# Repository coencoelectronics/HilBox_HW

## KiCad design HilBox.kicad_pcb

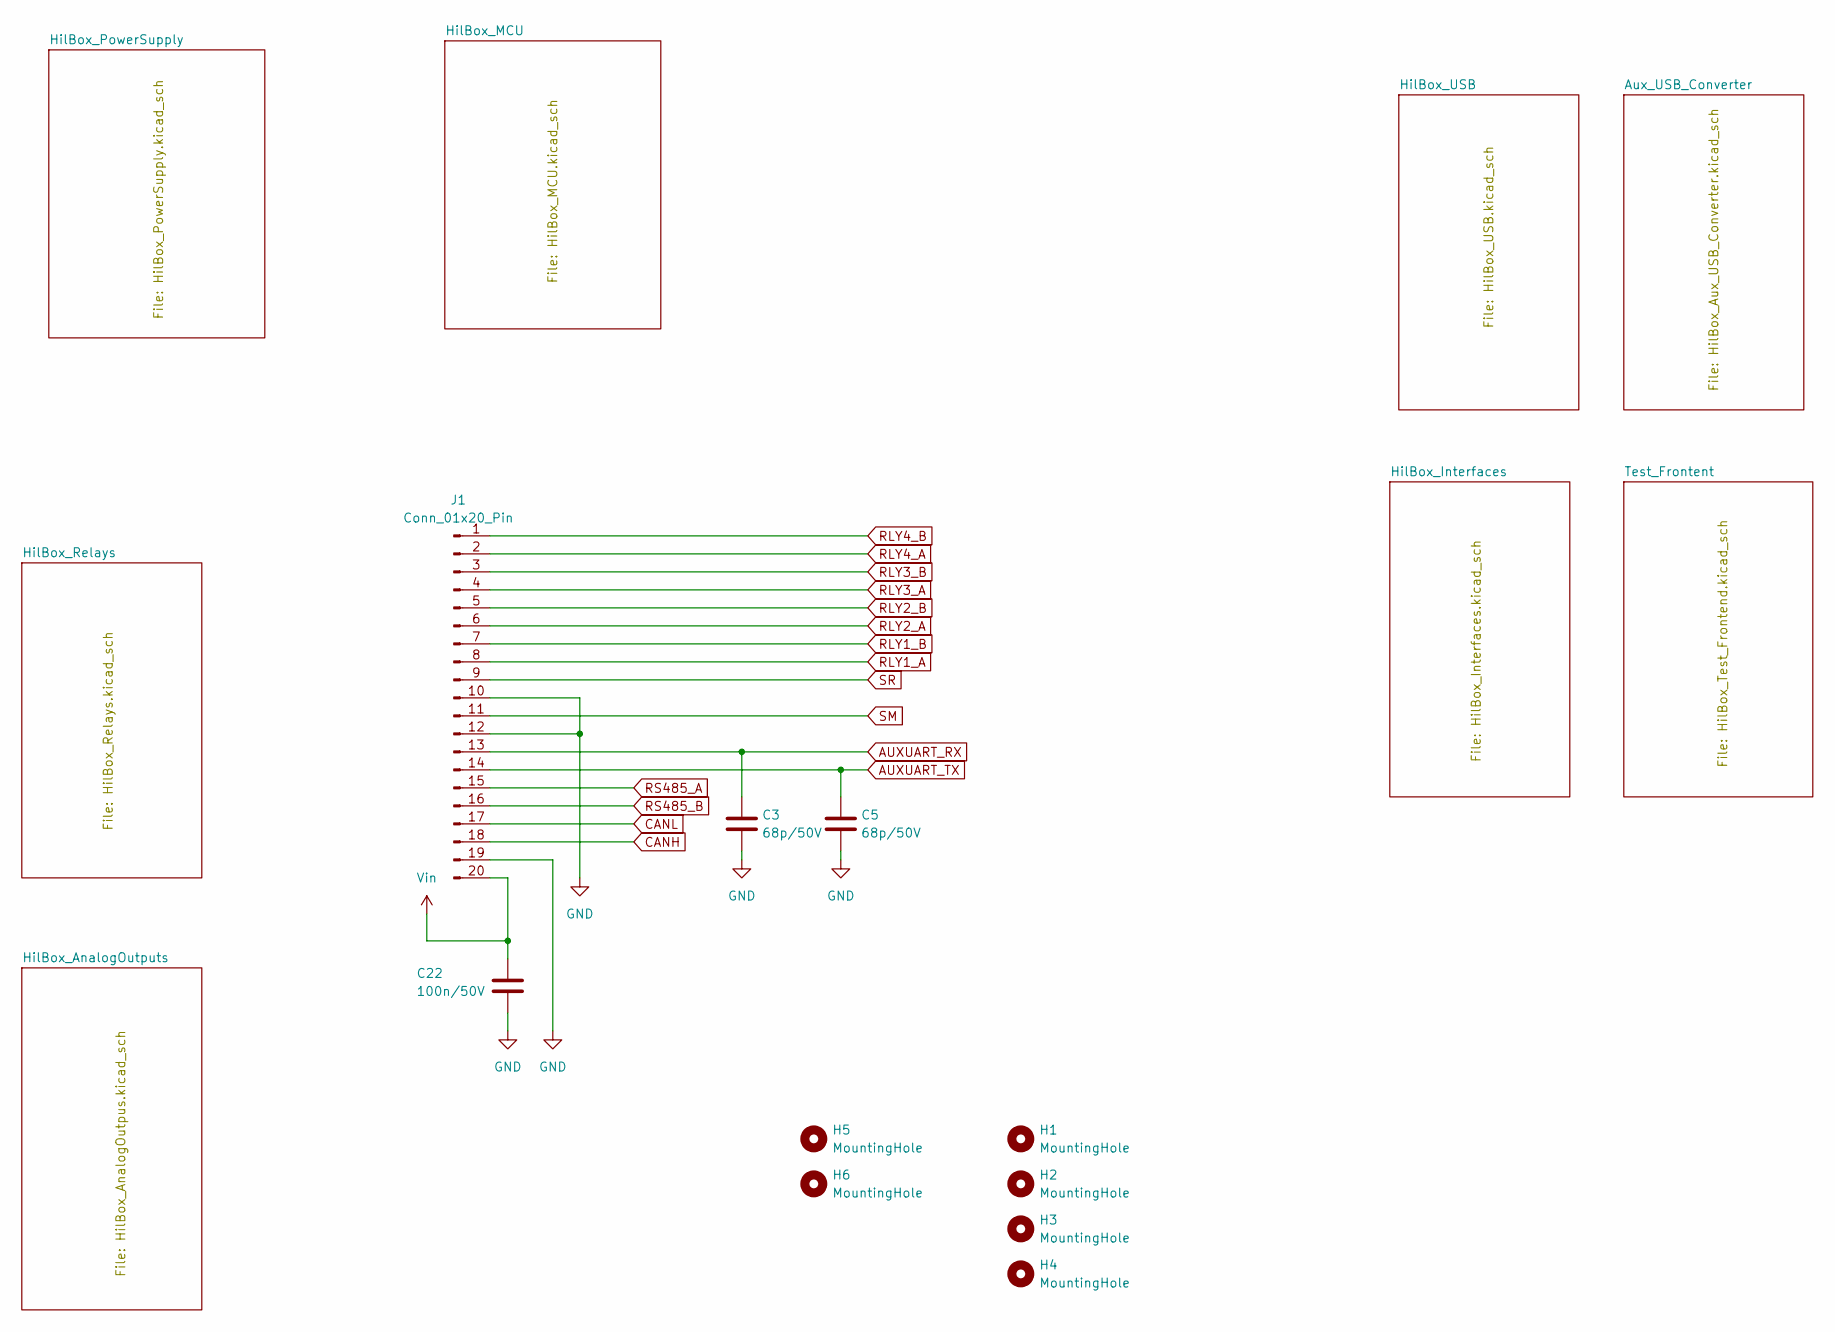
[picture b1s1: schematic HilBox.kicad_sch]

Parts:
C3, C5: 68p/50V; C_0402_1005Metric; JLC_PN C77014
C22: 100n/50V; C_0402_1005Metric; JLC_PN C77014
H1, H2, H3, H4: MountingHole; MountingHole_3.2mm_M3
H5, H6: MountingHole; MountingHole_2.2mm_M2
J1: Conn_01x20_Pin; Terminal_Block_3_81_20p_Horizontal; JLC_PN C430380

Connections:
AUXUART_RX: C3.1, J1.13; also elsewhere on the board
AUXUART_TX: C5.1, J1.14; also elsewhere on the board
CANH: J1.18; also elsewhere on the board
CANL: J1.17; also elsewhere on the board
GND: C3.2, C5.2, C22.2, J1.10, J1.12, J1.19; also elsewhere on the board
RLY1_A: J1.8; also elsewhere on the board
RLY1_B: J1.7; also elsewhere on the board
RLY2_A: J1.6; also elsewhere on the board
RLY2_B: J1.5; also elsewhere on the board
RLY3_A: J1.4; also elsewhere on the board
RLY3_B: J1.3; also elsewhere on the board
RLY4_A: J1.2; also elsewhere on the board
RLY4_B: J1.1; also elsewhere on the board
RS485_A: J1.15; also elsewhere on the board
RS485_B: J1.16; also elsewhere on the board
SM: J1.11; also elsewhere on the board
SR: J1.9; also elsewhere on the board
Vin: C22.1, J1.20; also elsewhere on the board

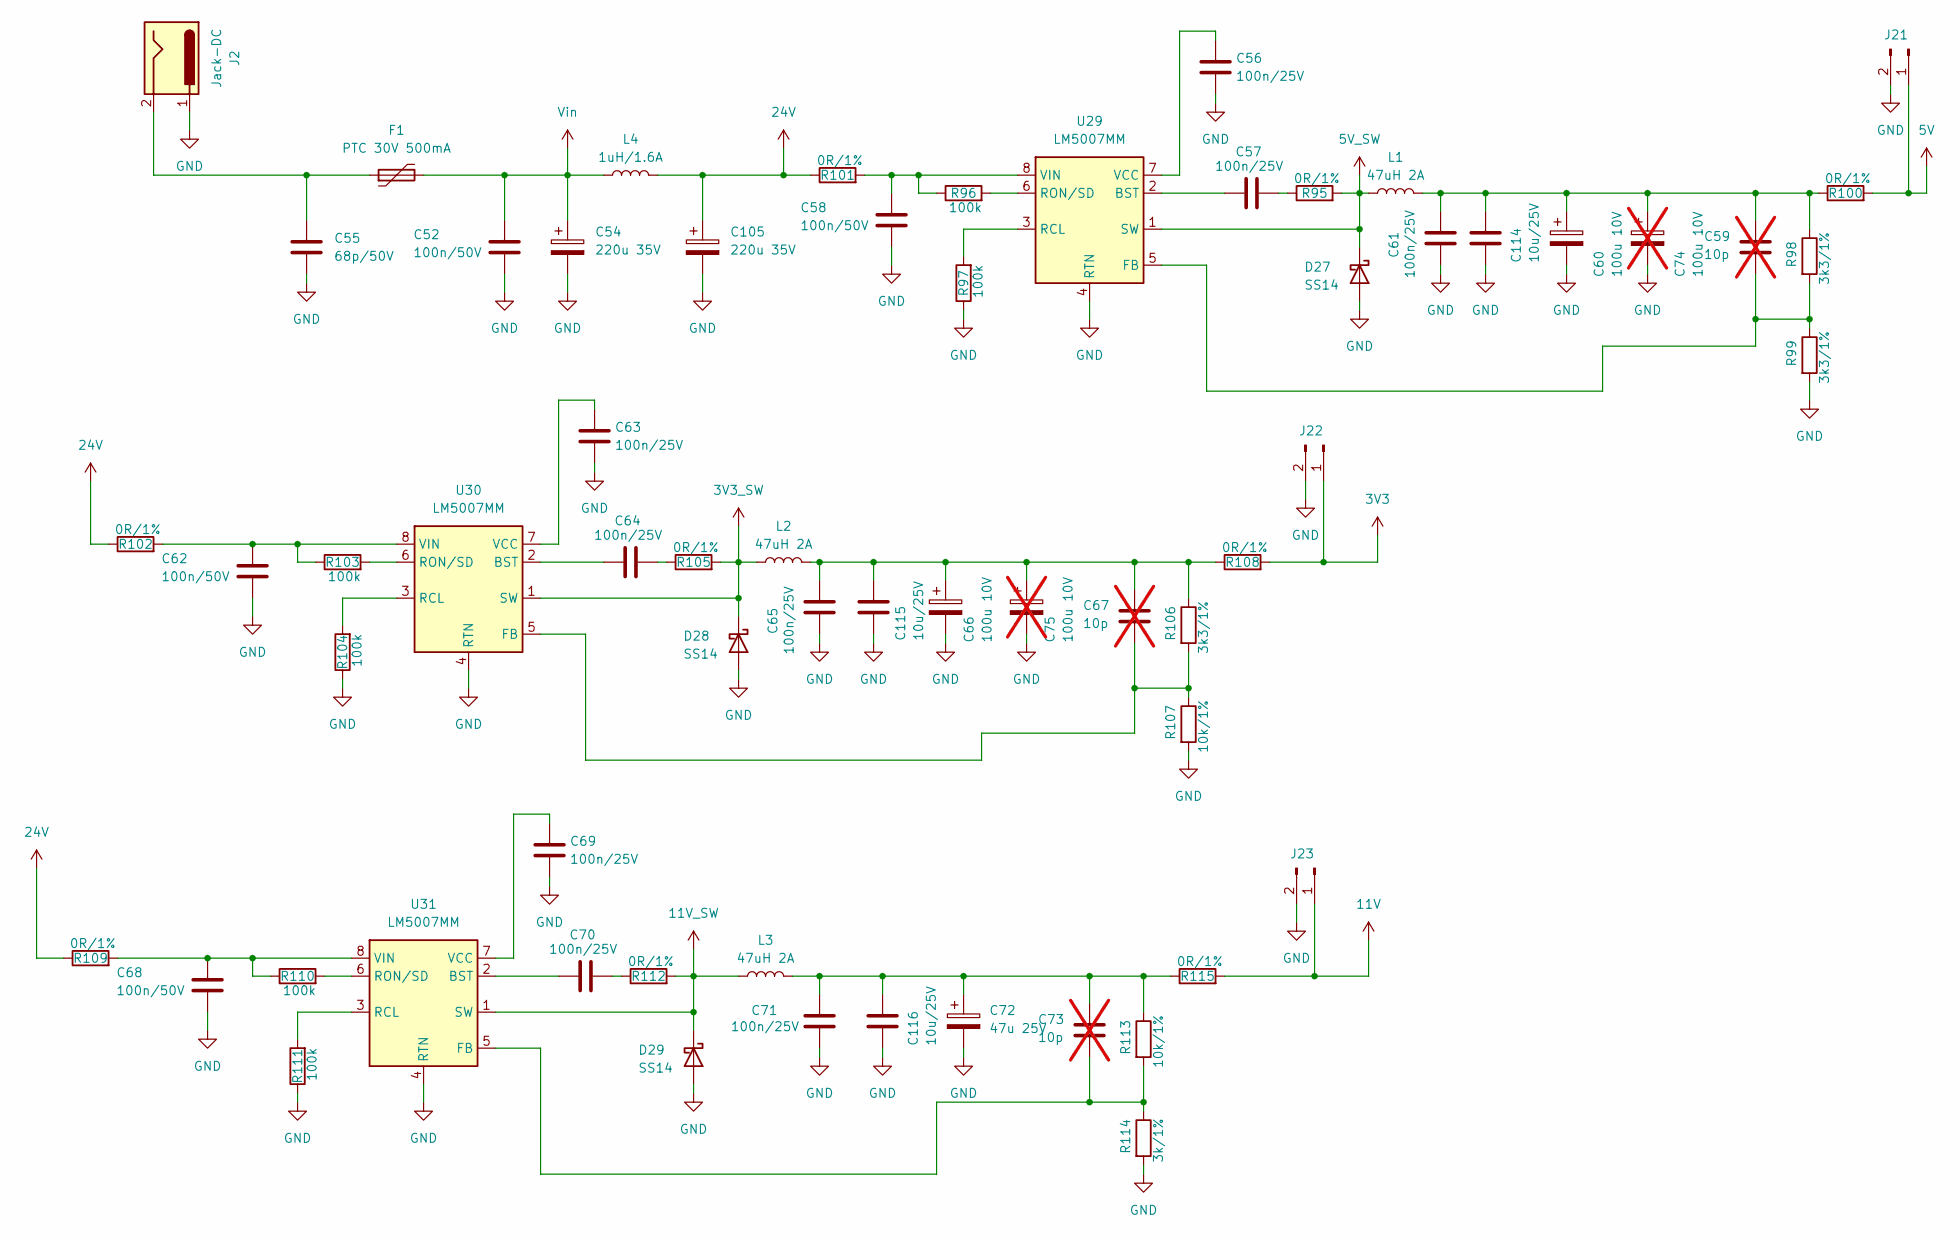
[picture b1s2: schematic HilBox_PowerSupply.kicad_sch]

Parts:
C52, C58, C62, C68: 100n/50V; C_0402_1005Metric; JLC_PN C77014
C54, C105: 220u 35V; CP_Elec_8x10.5; JLC_PN C3340
C55: 68p/50V; C_0402_1005Metric; JLC_PN C77014
C56, C57, C61, C63, C64, C65, C69, C70, C71: 100n/25V; C_0402_1005Metric; JLC_PN C77014
C59, C67, C73: 10p; C_0402_1005Metric; JLC_PN C77014; not fitted
C60, C66: 100u 10V; CP_Elec_5x5.3; JLC_PN C3347
C72: 47u 25V; CP_Elec_6.3x5.4; JLC_PN C30034
C74, C75: 100u 10V; CP_Elec_5x5.3; JLC_PN C3347; not fitted
C114, C115, C116: 10u/25V; C_1206_3216Metric; JLC_PN C9807
D27, D28, D29: SS14; D_SMA; JLC_PN C2480
F1: PTC 30V 500mA; R_1812_4532Metric; JLC_PN C12559
J2: Jack-DC; BarrelJack_GCT_DCJ200-10-A_Horizontal; JLC_PN C194407
J21, J22, J23: Conn_01x02_Pin; PinHeader_1x02_P2.54mm_Vertical; JLC_PN C225477
L1, L2, L3: 47uH 2A; L_Bourns_SRP7028A_7.3x6.6mm; JLC_PN C5189962
L4: 1uH/1.6A; L_1008_2520Metric; JLC_PN C86091
R95, R100, R101, R102, R105, R108, R109, R112, R115: 0R/1%; R_0603_1608Metric; JLC_PN C21189
R96, R97, R103, R104, R110, R111: 100k; R_0603_1608Metric; JLC_PN C15458
R98, R99, R106: 3k3/1%; R_0603_1608Metric; JLC_PN C22978
R107: 10k/1%; R_0603_1608Metric; JLC_PN C25804
R113: 10k/1%; R_0402_1005Metric; JLC_PN C25744
R114: 3k/1%; R_0603_1608Metric; JLC_PN C4211
U29, U30, U31: LM5007MM; VSSOP-8_3x3mm_P0.65mm; JLC_PN C9423

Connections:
3V3: J22.1, R108.2; also elsewhere on the board
3V3_SW: D28.1 (K), L2.1, R105.2, U30.1 (SW)
5V: J21.1, R100.2; also elsewhere on the board
5V_SW: D27.1 (K), L1.1, R95.2, U29.1 (SW)
11V: J23.1, R115.2; also elsewhere on the board
11V_SW: D29.1 (K), L3.1, R112.2, U31.1 (SW)
24V: C105.1, L4.2, R101.1, R102.1, R109.1
GND: C52.2, C54.2, C55.2, C56.2, C58.2, C60.2, C61.1, C62.2, C63.2, C65.1, C66.2, C68.2, C69.2, C71.1, C72.2, C74.2, C75.2, C105.2, C114.2, C115.2, C116.2, D27.2 (A), D28.2 (A), D29.2 (A), J2.1, J21.2, J22.2, J23.2, R97.1, R99.2, R104.1, R107.2, R111.1, R114.2, U29.4 (RTN), U30.4 (RTN), U31.4 (RTN); also elsewhere on the board
unnamed: C55.1, F1.1, J2.2
unnamed: C57.2, R95.1
unnamed: C64.2, R105.1
unnamed: C70.2, R112.1
unnamed: C59.1, C60.1, C61.2, C74.1, C114.1, L1.2, R98.1, R100.1
unnamed: C65.2, C66.1, C67.1, C75.1, C115.1, L2.2, R106.1, R108.1
unnamed: C71.2, C72.1, C73.1, C116.1, L3.2, R113.1, R115.1
unnamed: C57.1, U29.2 (BST)
unnamed: C59.2, R98.2, R99.1, U29.5 (FB)
unnamed: R97.2, U29.3 (RCL)
unnamed: R96.2, U29.6 (RON/SD)
unnamed: C56.1, U29.7 (VCC)
unnamed: C58.1, R96.1, R101.2, U29.8 (VIN)
unnamed: C64.1, U30.2 (BST)
unnamed: C67.2, R106.2, R107.1, U30.5 (FB)
unnamed: R104.2, U30.3 (RCL)
unnamed: R103.2, U30.6 (RON/SD)
unnamed: C63.1, U30.7 (VCC)
unnamed: C62.1, R102.2, R103.1, U30.8 (VIN)
unnamed: C70.1, U31.2 (BST)
unnamed: C73.2, R113.2, R114.1, U31.5 (FB)
unnamed: R111.2, U31.3 (RCL)
unnamed: R110.2, U31.6 (RON/SD)
unnamed: C69.1, U31.7 (VCC)
unnamed: C68.1, R109.2, R110.1, U31.8 (VIN)
Vin: C52.1, C54.1, F1.2, L4.1; also elsewhere on the board

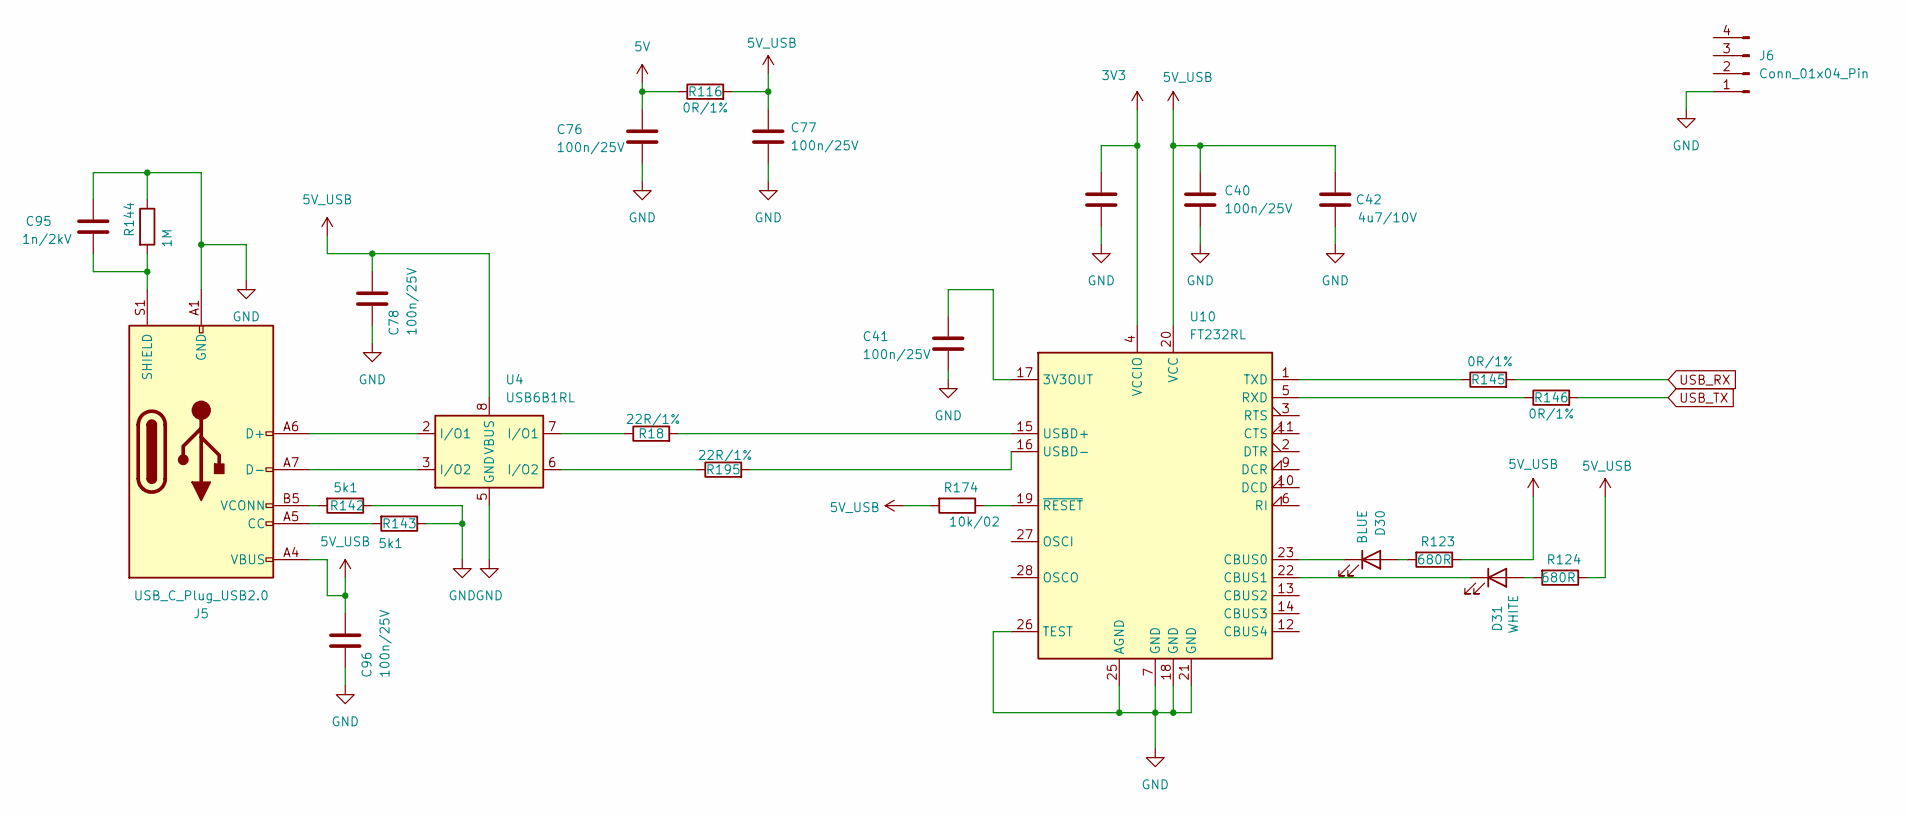
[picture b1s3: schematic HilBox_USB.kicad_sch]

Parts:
C39, C40, C41, C76, C77, C78, C96: 100n/25V; C_0402_1005Metric; JLC_PN C77014
C42: 4u7/10V; C_0402_1005Metric; JLC_PN C23733
C95: 1n/2kV; C_1206_3216Metric; JLC_PN C23631
D30: BLUE; LED_0603_1608Metric; JLC_PN C2288
D31: WHITE; LED_0603_1608Metric; JLC_PN C2290
J5: USB_C_Plug_USB2.0; USB_C_Receptacle_GCT_USB4105-xx-A_16P_TopMnt_Horizontal; JLC_PN C393939
J6: Conn_01x04_Pin
R18, R195: 22R/1%; R_0402_1005Metric; JLC_PN C25092
R116, R145, R146: 0R/1%; R_0603_1608Metric; JLC_PN C21189
R123, R124: 680R; R_0603_1608Metric; JLC_PN C25177
R142, R143: 5k1; R_0603_1608Metric; JLC_PN C23162
R144: 1M; R_0603_1608Metric; JLC_PN C22935
R174: 10k/02; R_0402_1005Metric; JLC_PN C25531
U4: USB6B1RL; SOIC-8_3.9x4.9mm_P1.27mm
U10: FT232RL; SSOP-28_5.3x10.2mm_P0.65mm; JLC_PN C5246810

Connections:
3V3: C39.1, U10.4 (VCCIO); also elsewhere on the board
5V: C76.1, R116.1; also elsewhere on the board
5V_USB: C40.1, C42.1, C77.1, C78.1, C96.1, J5.A4 (VBUS), J5.A9 (VBUS), J5.B4 (VBUS), J5.B9 (VBUS), R116.2, R123.1, R124.1, R174.2, U4.1 (VBUS), U4.8 (VBUS), U10.20 (VCC)
GND: C39.2, C40.2, C41.2, C42.2, C76.2, C77.2, C78.2, C95.1, C96.2, J5.A1 (GND), J5.A12 (GND), J5.B1 (GND), J5.B12 (GND), R142.1, R143.1, R144.1, U4.4 (GND), U4.5 (GND), U10.7 (GND), U10.18 (GND), U10.21 (GND), U10.25 (AGND), U10.26 (TEST); also elsewhere on the board
unnamed: D30.2 (A), R123.2
unnamed: D30.1 (K), U10.23 (CBUS0)
unnamed: D31.2 (A), R124.2
unnamed: D31.1 (K), U10.22 (CBUS1)
unnamed: J5.A5 (CC), R143.2
unnamed: J5.A6 (D+), U4.2 (I/O1)
unnamed: J5.A7 (D-), U4.3 (I/O2)
unnamed: C95.2, J5.S1 (SHIELD), R144.2
unnamed: J5.B5 (VCONN), R142.2
unnamed: R18.1, U4.7 (I/O1)
unnamed: R195.1, U4.6 (I/O2)
unnamed: C41.1, U10.17 (3V3OUT)
unnamed: R146.1, U10.5 (RXD)
unnamed: R145.1, U10.1 (TXD)
unnamed: R18.2, U10.15 (USBD+)
unnamed: R195.2, U10.16 (USBD-)
unnamed: R174.1, U10.19 (~RESET)
USB_RX: R145.2; also elsewhere on the board
USB_TX: R146.2; also elsewhere on the board

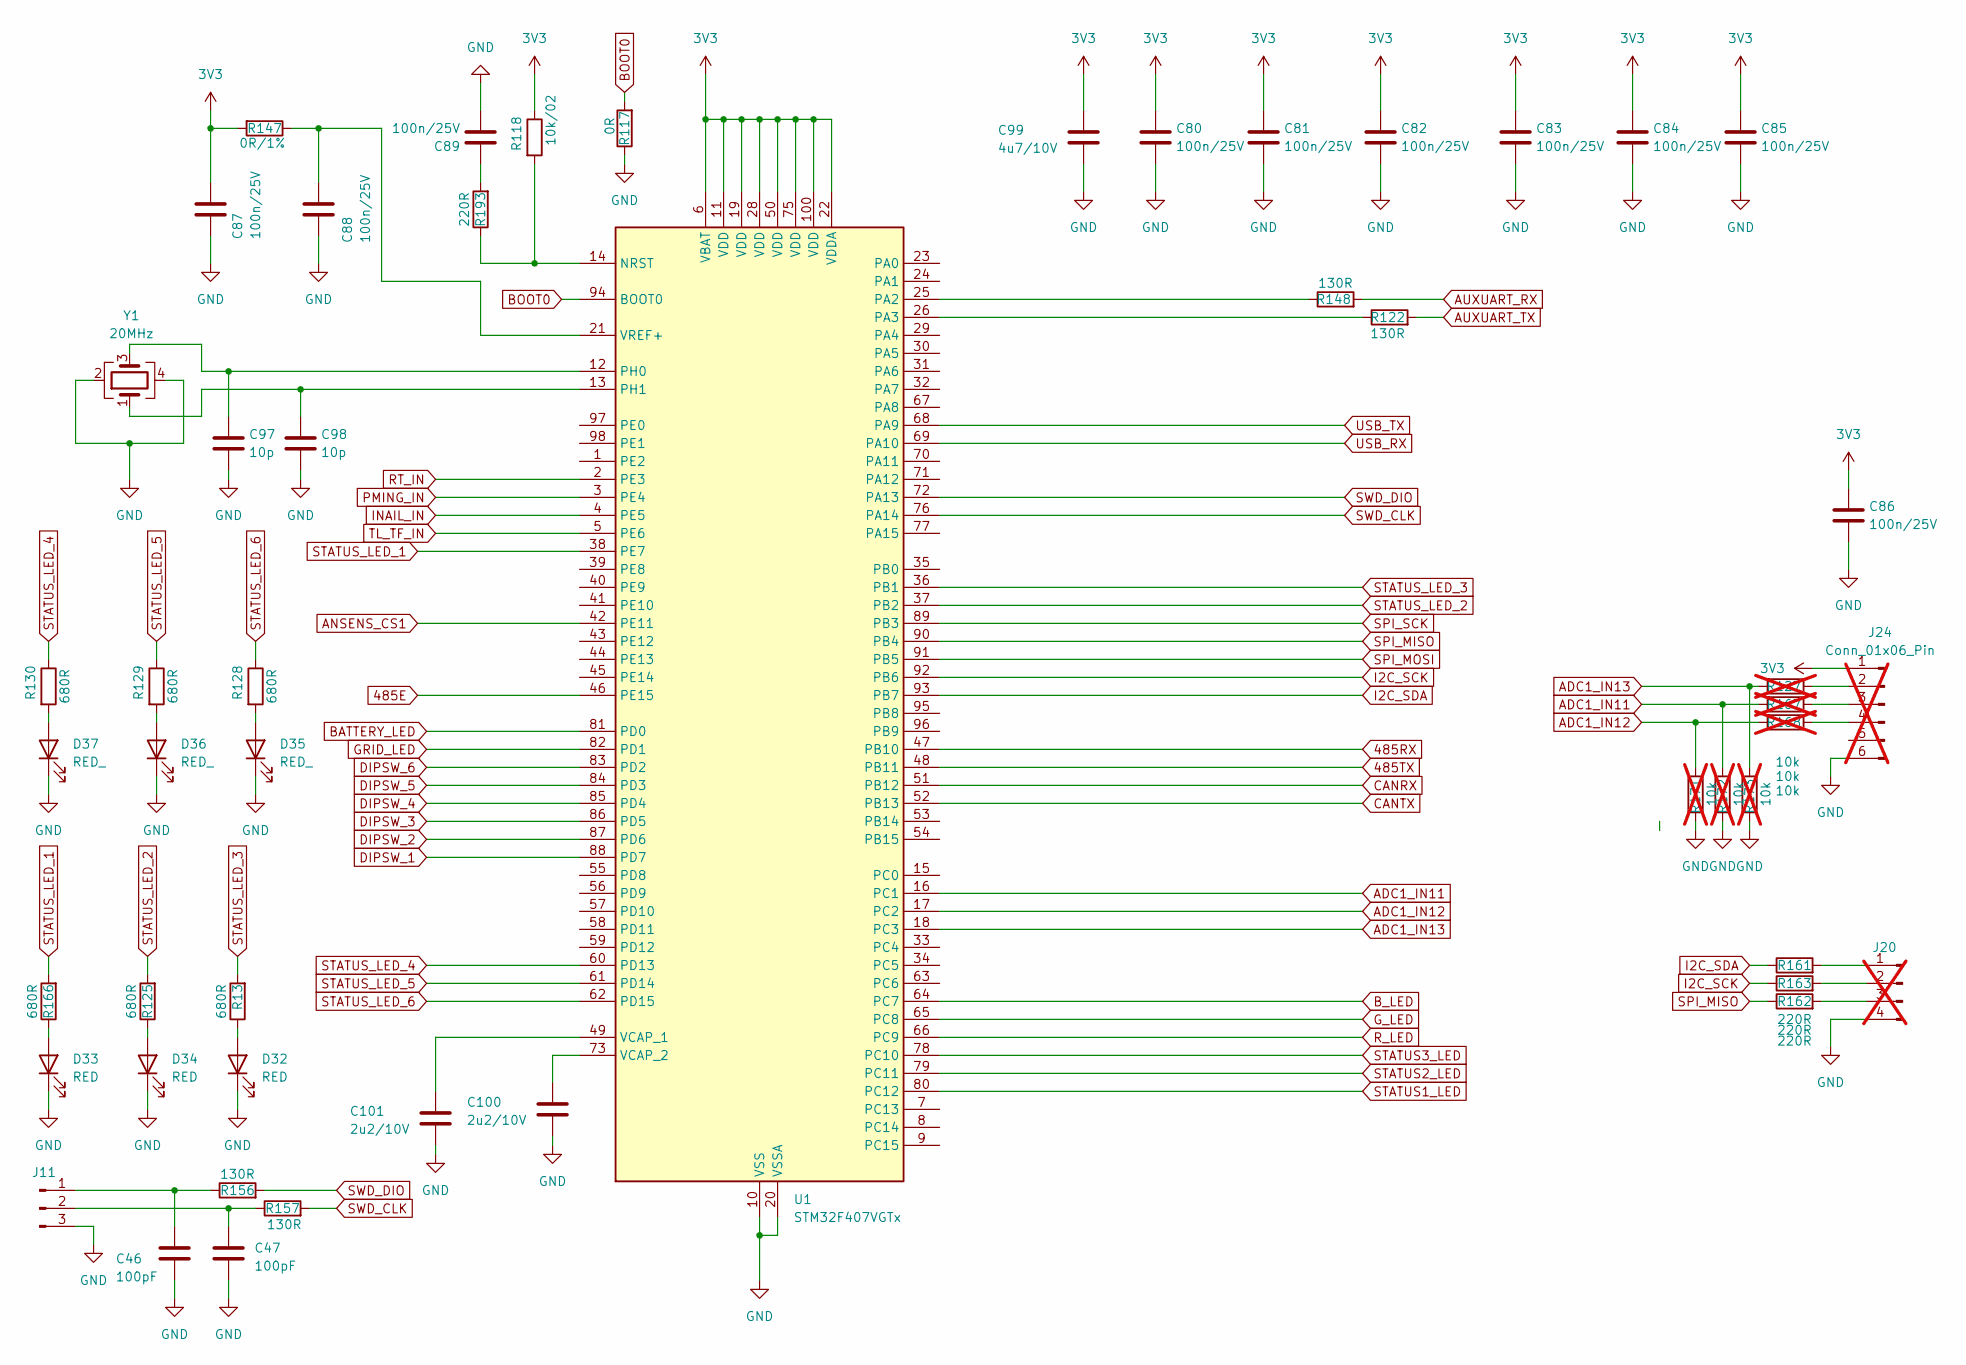
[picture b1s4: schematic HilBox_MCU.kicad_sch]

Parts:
C46, C47: 100pF; C_0402_1005Metric; JLC_PN C1546
C80, C81, C82, C83, C84, C85, C86, C87, C88, C89: 100n/25V; C_0402_1005Metric; JLC_PN C77014
C97, C98: 10p; C_0402_1005Metric; JLC_PN C1545
C99: 4u7/10V; C_0402_1005Metric; JLC_PN C23733
C100, C101: 2u2/10V; C_0402_1005Metric; JLC_PN C60078
D32: RED; LED_0603_1608Metric; JLC_PN C72038
D33, D34: RED; LED_0603_1608Metric; JLC_PN C2286
D35, D36, D37: RED_; LED_0603_1608Metric; JLC_PN C2286
J11: Conn_01x03_Pin; PinHeader_1x03_P2.54mm_Vertical; JLC_PN C49257
J20: Conn_01x04_Pin; PinHeader_2x02_P2.54mm_Vertical; not fitted
J24: Conn_01x06_Pin; PinHeader_2x03_P2.54mm_Vertical; not fitted
R13, R125, R166: 680R; R_0402_1005Metric; JLC_PN C25177
R117: 0R; R_0402_1005Metric; JLC_PN C17168
R118: 10k/02; R_0402_1005Metric; JLC_PN C25531
R122, R148, R156, R157: 130R; R_0603_1608Metric; JLC_PN C22796
R127, R167, R168, R171, R172, R173: 10k; R_0402_1005Metric; JLC_PN C25531; not fitted
R128, R129, R130: 680R; R_0603_1608Metric; JLC_PN C25177
R147: 0R/1%; R_0603_1608Metric; JLC_PN C21189
R161, R162, R163, R193: 220R; R_0402_1005Metric; JLC_PN C1091
U1: STM32F407VGTx; LQFP-100_14x14mm_P0.5mm; JLC_PN C12345
Y1: 20MHz; Crystal_SMD_2016-4Pin_2.0x1.6mm; JLC_PN C1985446

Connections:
3V3: C80.1, C81.1, C82.1, C83.1, C84.1, C85.1, C86.1, C87.1, C99.1, J24.1, R118.1, R147.2, U1.6 (VBAT), U1.11 (VDD), U1.19 (VDD), U1.22 (VDDA), U1.28 (VDD), U1.50 (VDD), U1.75 (VDD), U1.100 (VDD); also elsewhere on the board
485E: U1.46 (PE15); also elsewhere on the board
485RX: U1.47 (PB10); also elsewhere on the board
485TX: U1.48 (PB11); also elsewhere on the board
ADC1_IN11: R167.2, R172.1, U1.16 (PC1)
ADC1_IN12: R168.2, R171.1, U1.17 (PC2)
ADC1_IN13: R127.2, R173.1, U1.18 (PC3)
ANSENS_CS1: U1.42 (PE11); also elsewhere on the board
AUXUART_RX: R148.2; also elsewhere on the board
AUXUART_TX: R122.2; also elsewhere on the board
BATTERY_LED: U1.81 (PD0); also elsewhere on the board
BOOT0: R117.2, U1.94 (BOOT0)
B_LED: U1.64 (PC7); also elsewhere on the board
CANRX: U1.51 (PB12); also elsewhere on the board
CANTX: U1.52 (PB13); also elsewhere on the board
DIPSW_1: U1.88 (PD7); also elsewhere on the board
DIPSW_2: U1.87 (PD6); also elsewhere on the board
DIPSW_3: U1.86 (PD5); also elsewhere on the board
DIPSW_4: U1.85 (PD4); also elsewhere on the board
DIPSW_5: U1.84 (PD3); also elsewhere on the board
DIPSW_6: U1.83 (PD2); also elsewhere on the board
GND: C46.2, C47.2, C80.2, C81.2, C82.2, C83.2, C84.2, C85.2, C86.2, C87.2, C88.2, C89.2, C97.2, C98.2, C99.2, C100.2, C101.2, D32.1 (K), D33.1 (K), D34.1 (K), D35.1 (K), D36.1 (K), D37.1 (K), J11.3, J20.4, J24.6, R117.1, R171.2, R172.2, R173.2, U1.10 (VSS), U1.20 (VSSA), U1.27 (VSS), U1.74 (VSS), U1.99 (VSS), Y1.2, Y1.4; also elsewhere on the board
GRID_LED: U1.82 (PD1); also elsewhere on the board
G_LED: U1.65 (PC8); also elsewhere on the board
I2C_SCK: R163.1, U1.92 (PB6)
I2C_SDA: R161.1, U1.93 (PB7)
INAIL_IN: U1.4 (PE5); also elsewhere on the board
unnamed: C89.1, R193.2
unnamed: D32.2 (A), R13.1
unnamed: D33.2 (A), R166.1
unnamed: D34.2 (A), R125.1
unnamed: D35.2 (A), R128.2
unnamed: D36.2 (A), R129.2
unnamed: D37.2 (A), R130.2
unnamed: C46.1, J11.1, R156.1
unnamed: C47.1, J11.2, R157.1
unnamed: J20.1, R161.2
unnamed: J20.2, R163.2
unnamed: J20.3, R162.2
unnamed: J24.2, R127.1
unnamed: J24.3, R167.1
unnamed: J24.4, R168.1
unnamed: R118.2, R193.1, U1.14 (NRST)
unnamed: R148.1, U1.25 (PA2)
unnamed: R122.1, U1.26 (PA3)
unnamed: C97.1, U1.12 (PH0), Y1.3
unnamed: C98.1, U1.13 (PH1), Y1.1
unnamed: C101.1, U1.49 (VCAP_1)
unnamed: C100.1, U1.73 (VCAP_2)
unnamed: C88.1, R147.1, U1.21 (VREF+)
PMING_IN: U1.3 (PE4); also elsewhere on the board
RT_IN: U1.2 (PE3); also elsewhere on the board
R_LED: U1.66 (PC9); also elsewhere on the board
SPI_MISO: R162.1, U1.90 (PB4)
SPI_MOSI: U1.91 (PB5); also elsewhere on the board
SPI_SCK: U1.89 (PB3); also elsewhere on the board
STATUS1_LED: U1.80 (PC12); also elsewhere on the board
STATUS2_LED: U1.79 (PC11); also elsewhere on the board
STATUS3_LED: U1.78 (PC10); also elsewhere on the board
STATUS_LED_1: R166.2, U1.38 (PE7)
STATUS_LED_2: R125.2, U1.37 (PB2)
STATUS_LED_3: R13.2, U1.36 (PB1)
STATUS_LED_4: R130.1, U1.60 (PD13)
STATUS_LED_5: R129.1, U1.61 (PD14)
STATUS_LED_6: R128.1, U1.62 (PD15)
SWD_CLK: R157.2, U1.76 (PA14)
SWD_DIO: R156.2, U1.72 (PA13)
TL_TF_IN: U1.5 (PE6); also elsewhere on the board
USB_RX: U1.69 (PA10); also elsewhere on the board
USB_TX: U1.68 (PA9); also elsewhere on the board

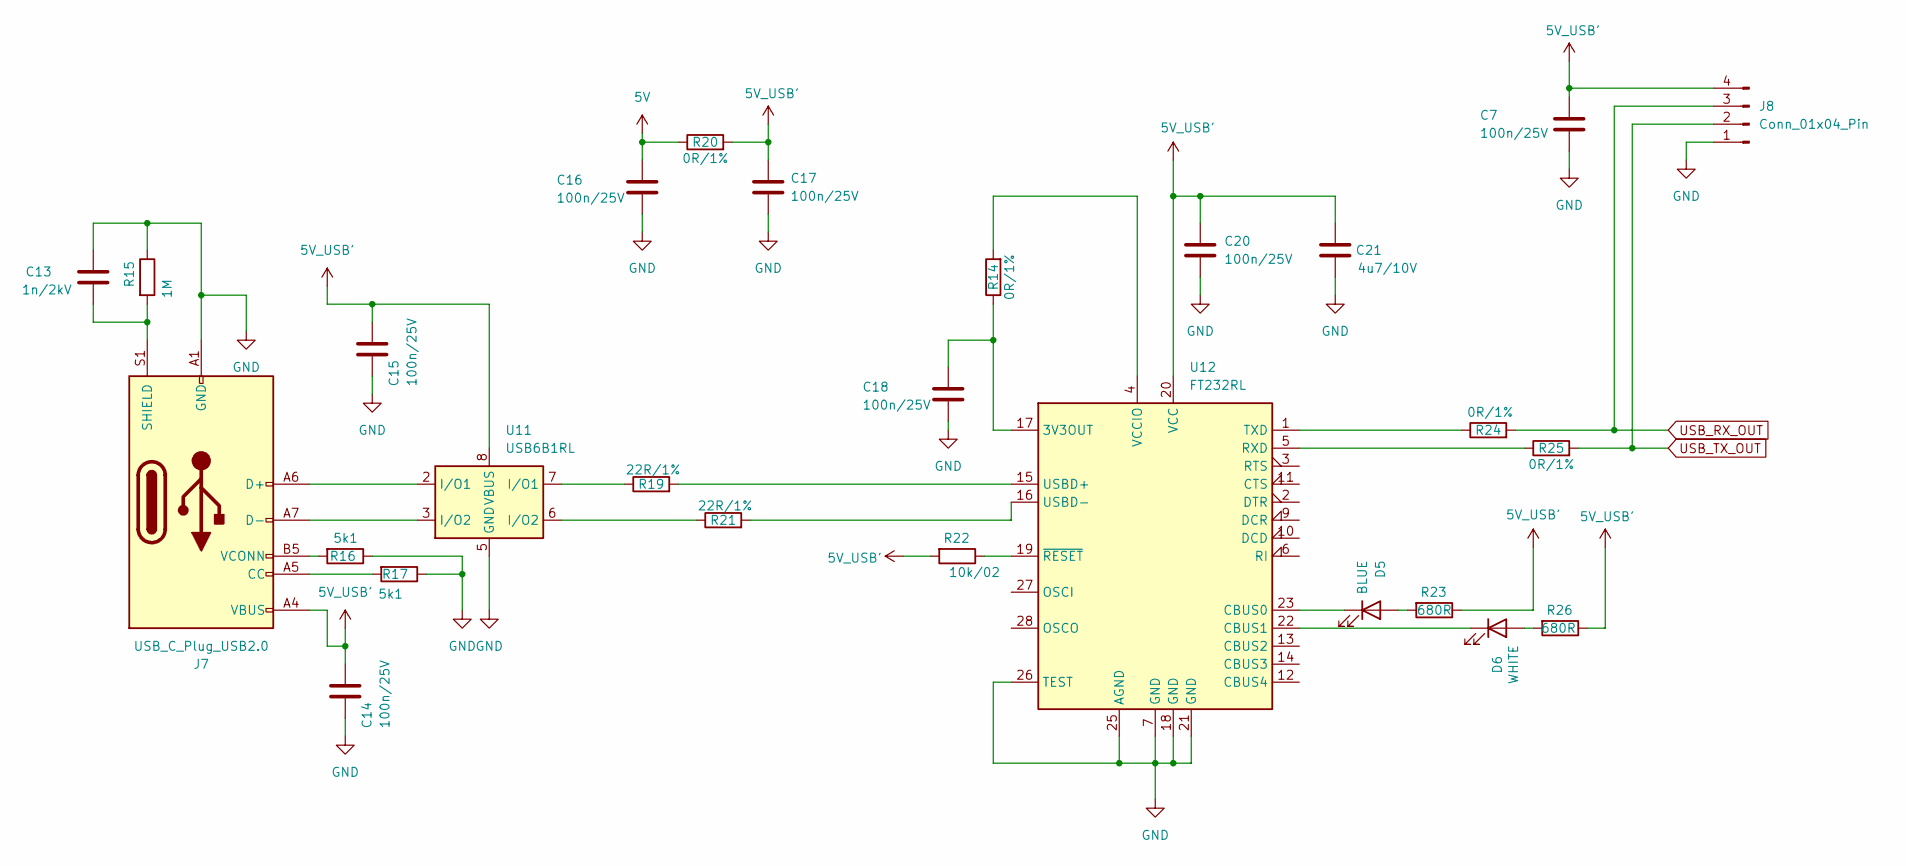
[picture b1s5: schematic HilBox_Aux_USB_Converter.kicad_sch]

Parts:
C7, C14, C15, C16, C17, C18, C20: 100n/25V; C_0402_1005Metric; JLC_PN C77014
C13: 1n/2kV; C_1206_3216Metric; JLC_PN C23631
C21: 4u7/10V; C_0402_1005Metric; JLC_PN C23733
D5: BLUE; LED_0603_1608Metric; JLC_PN C2288
D6: WHITE; LED_0603_1608Metric; JLC_PN C2290
J7: USB_C_Plug_USB2.0; USB_C_Receptacle_GCT_USB4105-xx-A_16P_TopMnt_Horizontal; JLC_PN C393939
J8: Conn_01x04_Pin; PinHeader_1x04_P2.54mm_Vertical; JLC_PN C7430360
R14, R20, R24, R25: 0R/1%; R_0603_1608Metric; JLC_PN C21189
R15: 1M; R_0603_1608Metric; JLC_PN C22935
R16, R17: 5k1; R_0603_1608Metric; JLC_PN C23162
R19, R21: 22R/1%; R_0402_1005Metric; JLC_PN C25092
R22: 10k/02; R_0402_1005Metric; JLC_PN C25531
R23, R26: 680R; R_0603_1608Metric; JLC_PN C25177
U11: USB6B1RL; SOIC-8_3.9x4.9mm_P1.27mm
U12: FT232RL; SSOP-28_5.3x10.2mm_P0.65mm; JLC_PN C5246810

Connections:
5V: C16.1, R20.1; also elsewhere on the board
5V_USB': C7.1, C14.1, C15.1, C17.1, C20.1, C21.1, J7.A4 (VBUS), J7.A9 (VBUS), J7.B4 (VBUS), J7.B9 (VBUS), J8.4, R20.2, R22.2, R23.1, R26.1, U11.1 (VBUS), U11.8 (VBUS), U12.20 (VCC)
GND: C7.2, C13.1, C14.2, C15.2, C16.2, C17.2, C18.2, C20.2, C21.2, J7.A1 (GND), J7.A12 (GND), J7.B1 (GND), J7.B12 (GND), J8.1, R15.1, R16.1, R17.1, U11.4 (GND), U11.5 (GND), U12.7 (GND), U12.18 (GND), U12.21 (GND), U12.25 (AGND), U12.26 (TEST); also elsewhere on the board
unnamed: D5.2 (A), R23.2
unnamed: D5.1 (K), U12.23 (CBUS0)
unnamed: D6.2 (A), R26.2
unnamed: D6.1 (K), U12.22 (CBUS1)
unnamed: J7.A5 (CC), R17.2
unnamed: J7.A6 (D+), U11.2 (I/O1)
unnamed: J7.A7 (D-), U11.3 (I/O2)
unnamed: C13.2, J7.S1 (SHIELD), R15.2
unnamed: J7.B5 (VCONN), R16.2
unnamed: R19.1, U11.7 (I/O1)
unnamed: R21.1, U11.6 (I/O2)
unnamed: C18.1, R14.1, U12.17 (3V3OUT)
unnamed: R25.1, U12.5 (RXD)
unnamed: R24.1, U12.1 (TXD)
unnamed: R19.2, U12.15 (USBD+)
unnamed: R21.2, U12.16 (USBD-)
unnamed: R14.2, U12.4 (VCCIO)
unnamed: R22.1, U12.19 (~RESET)
USB_RX_OUT: J8.3, R24.2
USB_TX_OUT: J8.2, R25.2

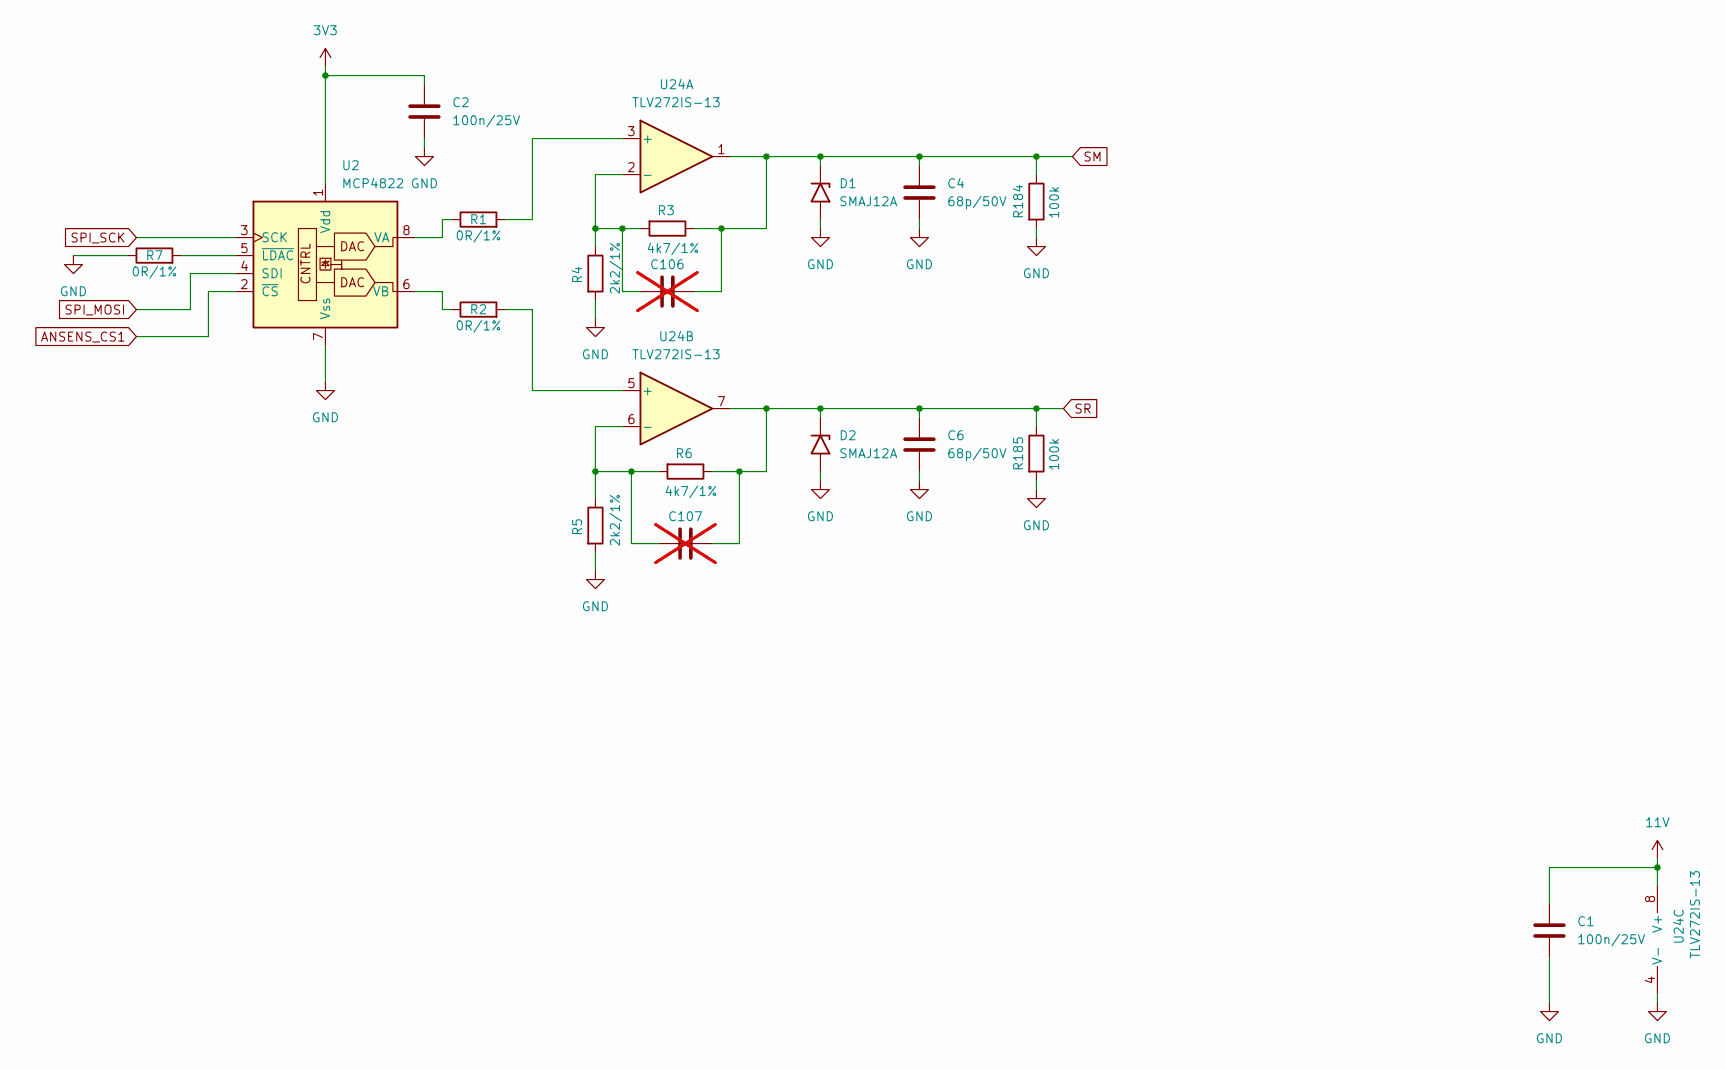
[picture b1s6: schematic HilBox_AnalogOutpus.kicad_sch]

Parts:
C1, C2: 100n/25V; C_0402_1005Metric; JLC_PN C77014
C4, C6: 68p/50V; C_0402_1005Metric; JLC_PN C77014
C106, C107: 10p; C_0402_1005Metric; JLC_PN C1545; not fitted
D1, D2: SMAJ12A; D_SMA; JLC_PN C113957
R1, R2, R7: 0R/1%; R_0603_1608Metric; JLC_PN C21189
R3, R6: 4k7/1%; R_0603_1608Metric; JLC_PN C23162
R4, R5: 2k2/1%; R_0603_1608Metric; JLC_PN C4190
R184, R185: 100k; R_0603_1608Metric; JLC_PN C15458
U2: MCP4822; SOIC-8_3.9x4.9mm_P1.27mm; JLC_PN C16040
U24: TLV272IS-13; VSSOP-8_3x3mm_P0.65mm; JLC_PN C23919

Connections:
3V3: C2.1, U2.1 (Vdd); also elsewhere on the board
11V: C1.1, U24.8 (V+); also elsewhere on the board
ANSENS_CS1: U2.2 (~CS); also elsewhere on the board
GND: C1.2, C2.2, C4.2, C6.2, D1.2 (A2), D2.2 (A2), R4.2, R5.2, R7.1, R184.2, R185.2, U2.7 (Vss), U24.4 (V-), U24.9 (V-); also elsewhere on the board
unnamed: R1.1, U2.8 (VA)
unnamed: R2.1, U2.6 (VB)
unnamed: R7.2, U2.5 (~LDAC)
unnamed: R1.2, U24.3 (+)
unnamed: C106.1, R3.2, R4.1, U24.2 (-)
unnamed: R2.2, U24.5 (+)
unnamed: C107.1, R5.1, R6.2, U24.6 (-)
SM: C4.1, C106.2, D1.1 (A1), R3.1, R184.1, U24.1; also elsewhere on the board
SPI_MOSI: U2.4 (SDI); also elsewhere on the board
SPI_SCK: U2.3 (SCK); also elsewhere on the board
SR: C6.1, C107.2, D2.1 (A1), R6.1, R185.1, U24.7; also elsewhere on the board
